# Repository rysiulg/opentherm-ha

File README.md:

Own implementation
Integration opemntherm co gas boiler to homeassistant
Covers in backgroung autodiscovery homeassistant mqtt climate controls also
CO Heat depends on NEWS temperature -it starts only if outside temp is below some value (default 2degC) -this temp is get from mqtt broker as averange NEWS temp.
Control is also available by www ;)
Default temp_NEWS have value 0 and default cutoff_NEWS is 2 so at defult heating is controlled, if from some reason communication is broke to mqqt to get new NEWS sensor than every temp_NEWS_interval_reduction_time_ms (default 30min) temp NEWS is reduced by 5% to finally get tempCutof value to enable heating.
Automode is control by room temp sensor and room temp target, heat mode is based on temperature CO pipe
In mqtt queue are double state value for dhw and double for boiler. eg. ch_state is centrah heat state with state reded from boiler, ch_state_software is software state which tells if we allow heat co. This is used for graphs -I use ch_state to make gradient on graph below Boiler temperature to see when boiler heated co, and flame status tells that boiler works.

Gets from mqtt broker
- temperature of NEWS (north, west south east averange temperature)
- state of working carbon heat co pump works -it disables hest to co

Built in similar interface like webserial, but on same websocket. autoscroll is on when slider is on bottom -in other case autoscroll in terminal is off ;) -it' is also possible to send some commands -i've done in 2 parts one is common for other modules ans other is for local project to be compatible with other projects ;)

Change to AsyncMQTT -by #define switch is possible to back to pubsync MQTT
added also #defined switch to be able on or off some module like arduino ota, influxdb etc.

ToDo:
Add histeresa to Boiler water and mayby for CO..
Add corrections to enable webupdate from bin file -but ota works well and stable for now ;)

Current UI on websockets:

for me it's working only local, remotelly over my VPN ;)

Old UI:

HomeAssistaNT:

Now updated version of http interface:

PLATFORM: Espressif 8266 (4.0.1) > WeMos D1 R2 and mini
HARDWARE: ESP8266 80MHz, 80KB RAM, 4MB Flash
PACKAGES:
 - framework-arduinoespressif8266 @ 3.30002.0 (3.0.2)
 - tool-esptool @ 1.413.0 (4.13)
 - tool-esptoolpy @ 1.30000.201119 (3.0.0)
 - tool-mklittlefs @ 1.203.210628 (2.3)
 - tool-mkspiffs @ 1.200.0 (2.0)
 - toolchain-xtensa @ 2.100300.210717 (10.3.0)
LDF: Library Dependency Finder -> https://bit.ly/configure-pio-ldf
LDF Modes: Finder ~ chain, Compatibility ~ soft
Found 43 compatible libraries
Scanning dependencies...
Dependency Graph
|-- ESPAsyncTCP-esphome @ 1.2.3
|-- ESPAsyncWebServer-esphome @ 2.1.0
|   |-- ESPAsyncTCP-esphome @ 1.2.3
|   |-- Hash @ 1.0
|   |-- ESP8266WiFi @ 1.0
|-- AsyncMqttClient-esphome @ 0.8.6
|   |-- ESPAsyncTCP-esphome @ 1.2.3
|-- ESP_DoubleResetDetector @ 1.3.1
|   |-- EEPROM @ 1.0
|   |-- LittleFS @ 0.1.0
|-- ESP8266 Influxdb @ 3.12.0
|   |-- ESP8266HTTPClient @ 1.2
|   |   |-- ESP8266WiFi @ 1.0
|   |-- ESP8266WiFi @ 1.0
|-- DallasTemperature @ 3.11.0
|   |-- OneWire @ 2.3.7
|-- OneWire @ 2.3.7
|-- OpenTherm Library @ 1.1.3
|-- ESP8266WiFi @ 1.0
|-- LittleFS @ 0.1.0
|-- ArduinoOTA @ 1.0
|   |-- ESP8266WiFi @ 1.0
|   |-- ESP8266mDNS @ 1.2
|   |   |-- ESP8266WiFi @ 1.0
|-- DNSServer @ 1.1.1
|   |-- ESP8266WiFi @ 1.0
|-- ESP8266HTTPClient @ 1.2
|   |-- ESP8266WiFi @ 1.0
|-- ESP8266mDNS @ 1.2
|   |-- ESP8266WiFi @ 1.0
|-- Hash @ 1.0
|-- Ticker @ 1.0
|-- EEPROM @ 1.0
Building in release mode
Compiling .pio\build\d1_mini\src\main.cpp.o
Linking .pio\build\d1_mini\firmware.elf
Retrieving maximum program size .pio\build\d1_mini\firmware.elf
Checking size .pio\build\d1_mini\firmware.elf
Advanced Memory Usage is available via "PlatformIO Home > Project Inspect"
RAM:   [=====     ]  54.7% (used 44840 bytes from 81920 bytes)
Flash: [======    ]  59.7% (used 623681 bytes from 1044464 bytes)

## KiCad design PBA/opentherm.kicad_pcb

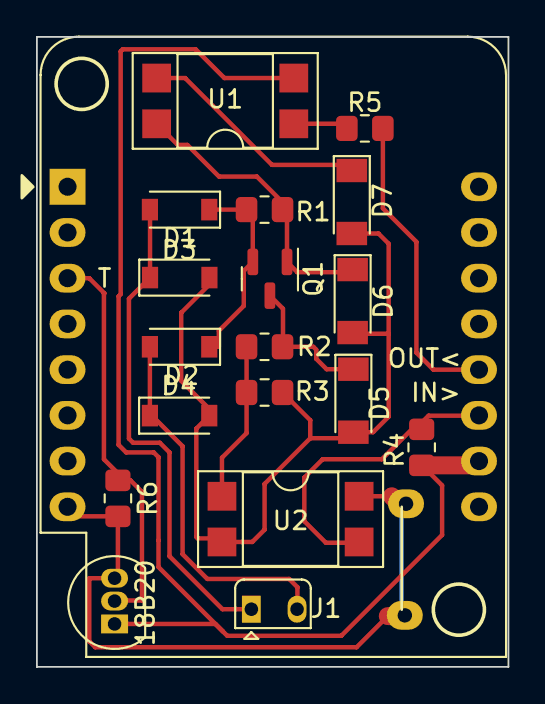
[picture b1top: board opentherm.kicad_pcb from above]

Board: 2 copper layers, 26.2 x 35.0 mm, 19 parts (0 on the bottom side), 14 nets.

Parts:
18B20: Conn_01x03; TO-92L_Inline
D1, D2, D3, D4: 1N4148W; D_SOD-123
D5: 4V7; D_MiniMELF
D6: 15v; D_MiniMELF
D7: 4V3; D_MiniMELF
J1: OT1_OT2; Heraeus_TO-92-2
Q1: BC858; SOT-23
R1, R5: 330; R_0805_2012Metric_Pad1.20x1.40mm_HandSolder
R2: 220; R_0805_2012Metric_Pad1.20x1.40mm_HandSolder
R3: 100; R_0805_2012Metric_Pad1.20x1.40mm_HandSolder
R4: 1k5; R_0805_2012Metric_Pad1.20x1.40mm_HandSolder
R6: 4k7; R_0805_2012Metric_Pad1.20x1.40mm_HandSolder
U1, U2: PC817; DIP-4_W7.62mm_SMDSocket_SmallPads
U3: WeMos_D1_mini; WEMOS_D1_mini_light

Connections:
GND: 18B20.1, R4.1, U1.2, U3.10 (GND)
unnamed: 18B20.2, R6.1, U3.3 (D0)
unnamed: D1.1 (K), D2.1 (K), Q1.2 (E), R1.1
unnamed: D3.1 (K), D4.1 (K), D5.2 (A), D6.2 (A), D7.2 (A), R3.2, U2.2
unnamed: D5.1 (K), Q1.3 (C), R2.1
unnamed: D6.1 (K), Q1.1 (B), R1.2, U1.4
unnamed: D7.1 (K), U1.3
unnamed: R2.2, R3.1, U2.1
unnamed: R5.1, U1.1
VCC: 18B20.3, R6.2, U2.4, U3.8 (3V3)
in: R5.2, U3.12 (D3)
ot1: D1.2 (A), D3.2 (A), J1.1
ot2: D2.2 (A), D4.2 (A), J1.2
out: R4.2, U2.3, U3.11 (D4)

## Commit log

2022-04-20 first commit-update
2022-04-20 Update config structure;)
2022-04-21 Add english translation and update www by slider to change values
2022-04-21 Update www and added in test mode flame energy consumed with mqtt send interval
2022-04-23 update sum of energy calculation
2022-04-24 added direct InfluxDB integration
2022-04-24 upda
2022-05-03 Change hostname and add listen topic from floor 1 and 2 and update room temp for control
2022-05-08 optimalization receive topics
2022-05-23 corrections change in gui cosmetics Update, Remove ArduinoJson and add my simple implementation to deserialize
2022-05-23 added PBA schematic for wemodD1
2022-05-23 Rename readmne.md to README.md
2022-05-24 korectioons
2022-05-24 increase mqtt update interval
2022-05-24 update gitignore
2022-06-05 update save routine
2022-06-05 add more commands to webserial receive dta
2022-06-12 corrections web dalltermometer link
2022-07-12 update code for universal purpose, change POST to WebSockets. Update web files from code to LittleFS and more
2022-07-13 update web with sliders
2022-07-14 finished update www, change and finish automode
2022-07-14 corection automode, almost finalne www, to do: mqtt control correction
2022-07-20 corrections. add possibility to send commands from serial ;)
2022-07-20 correction on received mqtt message from HA from automode, correction in flime time calculation
2022-07-20 update influx and mqtt time topic after change var types
2022-07-20 update www opcohi to dynamically cange when ecomode on/off
2022-07-21 add webserial on websocket, add menu html
2022-07-23 Batch update
2022-07-24 add config page and load/save settings
2022-07-26 correctoions
2022-07-29 added more commands and split function to const and local
2022-07-29 update remote commands. ToDo histereza CO + CWU?
2022-07-29 missing )
2022-07-29 missing message on delete config to recreate ;)
2022-07-30 corrections in read fs
2022-08-03 Add Histereaza to CWu and CO
2022-08-06 common changes ;)
2022-08-08 slight update mqtt
2022-08-09 corections and update common
2022-08-12 update, change OpenTherm to AsyncMode, remove yield from influx lib
2022-08-12 update corrections
2022-08-12 update spaces in code
2022-08-12 correction mqtt topics
2022-08-14 update mqtt will
2022-08-15 corrections mqtt
2022-08-22 correction of OT status message ;)
2022-08-27 last reset display corr
